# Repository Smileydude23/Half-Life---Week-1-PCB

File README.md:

hi this is my first time trying to design a pcb :D 
Introducing, the Smileybot...
It includes a small pet that you can interact with using two buttons. You can activate a play button and it will make a game of pong (FT3). There are also a variety of other options such as feeding and sleeping. 
I used KICAD to design both the schematic and the model for the PCB
The code was created in C++ through arduino IDE
Ignore the .CSV file in the Starbie file, it was automatically generated by KICAD and has no role

BOM chart:  

| Item                         | Qty | Supplier | Cost/item | Total Cost | Link                                                                                                                                                                                                                                                                                                                                                        |
| :--------------------------- | :-- | :------- | :-------- | :--------- | :---------------------------------------------------------------------------------------------------------------------------------------------------------------------------------------------------------------------------------------------------------------------------------------------------------------------------------------------------------- |
| DHT11                        | 1   | Amazon   | $1.70     | $1.70      | https://www.amazon.ca/gp/product/B0GM47D3HJ?smid=A3FRI6Z1EYRVHF&psc=1                                                                                                                                                                                                                                                                                       |
| ESP32-C3                     | 1   | Temu     | $2.27     | $2.27      | https://share.temu.com/JsLvWXTgjHA                                                                                                                                                                                                                                                                                                                          |
| OLED Display 128x64          | 1   | Temu     | $2.00     | $2.00      | https://share.temu.com/XOuxmemktiA                                                                                                                                                                                                                                                                                                                          |
| Switches (20 pack)           | 1   | Temu     | $1.64     | $1.64      | https://share.temu.com/ZJ8jJnzb3aA                                                                                                                                                                                                                                                                                                                          |
| MPU6050 Module and 01x08 pin | 1   | Temu     | $1.61     | $1.61      | https://share.temu.com/8b2jcn3grKA                                                                                                                                                                                                                                                                                                                          |
| Resistor Variety Pack        | 1   | Temu     | $2.24     | $2.24      | https://share.temu.com/8b2jcn3grKA                                                                                                                                                                                                                                                                                                                          |
| Keycaps (10 pack)            | 1   | Temu     | $1.26     | $1.26      | https://share.temu.com/h7hxsF63sEA                                                                                                                                                                                                                                                                                                                          |
| Solder                       | 1   | Amazon   | $1.05     | $1.05      | https://www.amazon.ca/Soldering-Welding-Promotion-Durable-Processing/dp/B0GFMXMZ36/ref=asc_df_B0GFMXMZ36?mcid=ec6c8f5b65b9309c909ac1eae124a0c6&tag=googleshopc0c-20&linkCode=df0&hvadid=797178855543&hvpos=&hvnetw=g&hvrand=15208472311860770710&hvpone=&hvptwo=&hvqmt=&hvdev=c&hvdvcmdl=&hvlocint=&hvlocphy=9001495&hvtargid=pla-2467980131731&psc=1&hvocijid=15208472311860770710-B0GFMXMZ36-&hvexpln=0&gad_source=1 |
| USB-C Port                   | 1   | Temu     | $2.84     | $2.84      | https://share.temu.com/IRJl58UtMLA                                                                                                                                                                                                                                                                                                                          |
| PCB Fabrication              | 1   | JLCPCB   | $4.00     | $4.00      | https://jlcpcb.com                                                                                                                                                                                                                                                                                                                                          |
| Estimated total shipping     | 1   |          |           | $5.74      |                                                                                                                                                                                                                                                                                                                                                             |

As of 2026/11/10 I have updated the PCB. These are images after edits for the first revision has been made. New wiring, moved XIAO, and silkscreen.

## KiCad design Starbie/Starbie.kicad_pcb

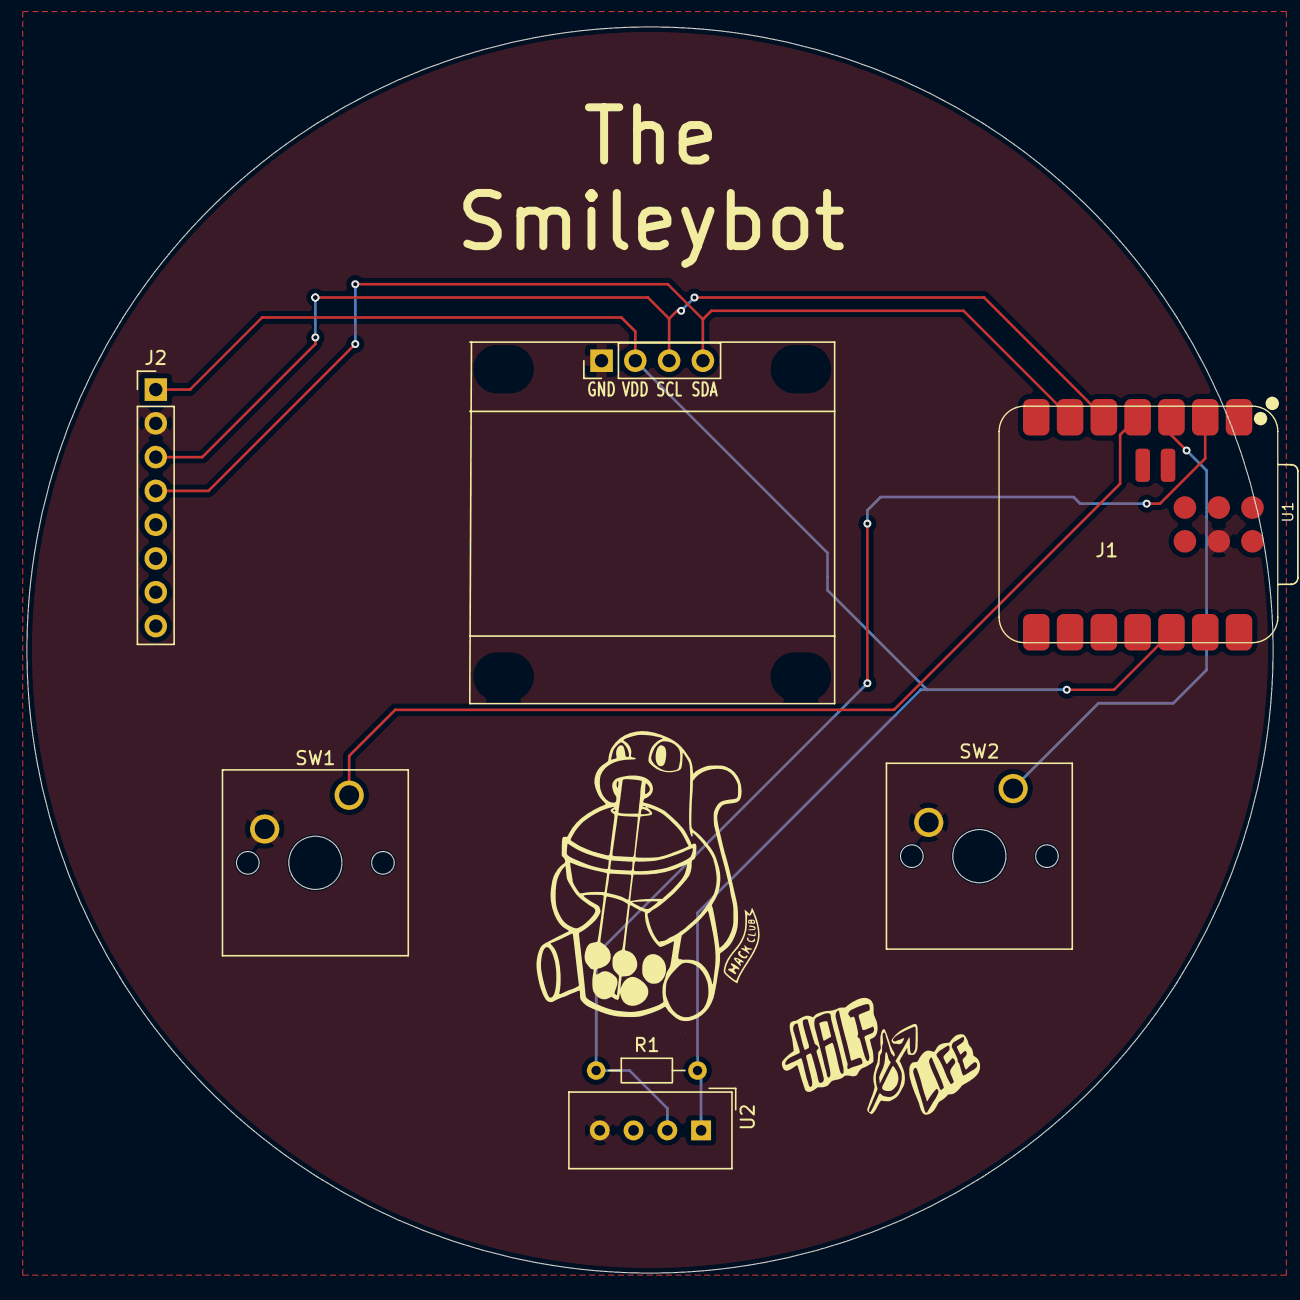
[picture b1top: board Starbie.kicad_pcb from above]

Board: 2 copper layers, 93.7 x 93.7 mm, 7 parts (0 on the bottom side), 7 nets.

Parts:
J1: Conn_01x04_Pin; Display_128x64_096_I2C
J2: Conn_01x08_Pin; PinHeader_1x08_P2.54mm_Vertical
R1: 10k; R_Axial_DIN0204_L3.6mm_D1.6mm_P7.62mm_Horizontal
SW1, SW2: SW_Push; SW_Cherry_MX_1.00u_PCB
U1: XIAO-ESP32-C3-SMD
U2: DHT11; Aosong_DHT11_5.5x12.0_P2.54mm

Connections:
+3.3V: J1.2, J2.1, R1.2, U1.12 (3V3_OUT), U2.1 (VDD)
/DHT11 DATA: R1.1, U1.2 (D1), U2.2 (DATA)
/GP102: SW2.1, U1.3 (D2)
/GP103: SW1.1, U1.4 (D3)
/SCL: J1.3, J2.3, U1.5 (D4)
/SDA: J1.4, J2.4, U1.6 (D5)
GND: J1.1, J2.2, SW1.2, SW2.2, U1.13 (GND), U1.18 (GND), U2.4 (GND)
